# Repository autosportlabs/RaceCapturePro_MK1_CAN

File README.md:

CAN for RaceCapture/Pro MK1
====

CAN Bus interface module for RaceCapture/Pro MK1 only. This adds a single CAN bus interface channel that integrates with the SPI interface available on RJ45 port. 

See the LICENSE.txt for information on the technology license

Autosport Labs
http://www.autosportlabs.com

Building the CANx board
=======================

Parts are defined in the CANx.csv. 

* All resistors are 0603 5%
* All capacitors are 0603 X7R

Connecting CANx
===============

Connect a short (6" or shorter) RJ45 cable with pins wired straight through between RaceCapture/Pro MK1 and the X2 port of CANx. A simple ethernet 6" extension cable should work fine. 

The CAN bus connection is available on X1 and conforms to the same pinout as RaceCapture/Pro MK2. And, you can use the same CAN->OBDII cable used on the newer versions of RaceCapture/Pro.

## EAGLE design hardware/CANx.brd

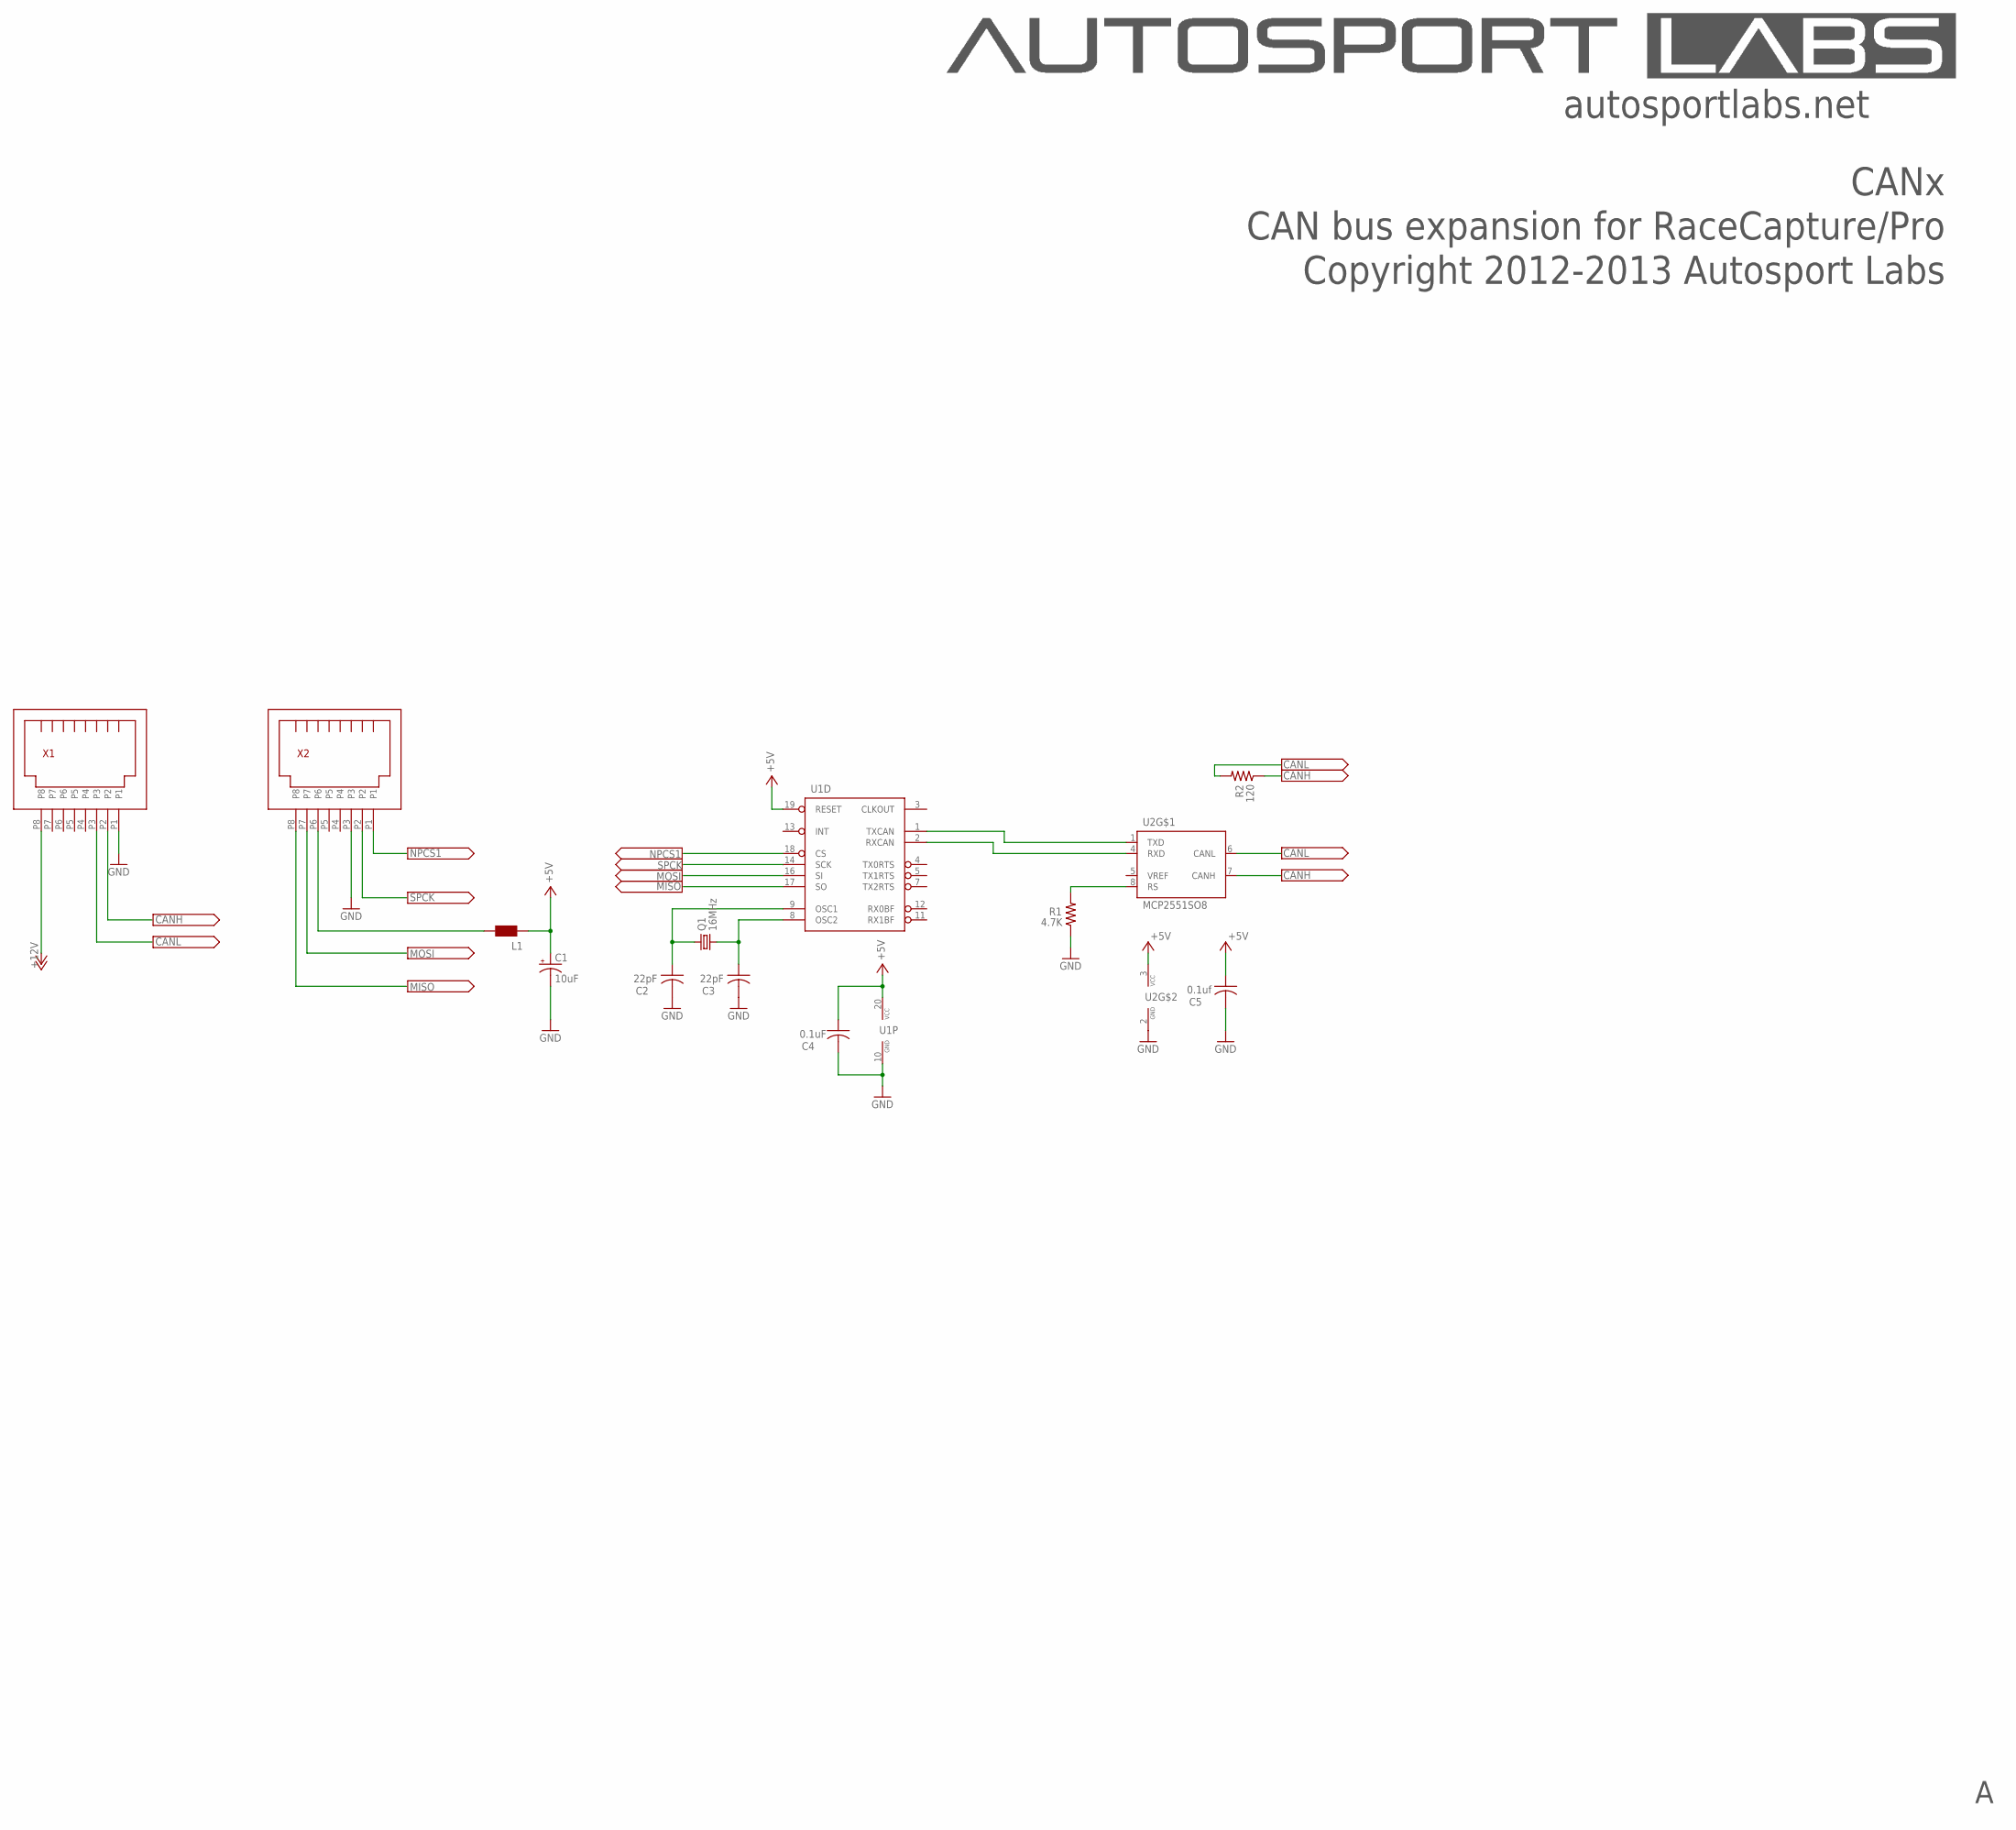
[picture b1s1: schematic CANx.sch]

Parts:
C1: 10uF; SMC_D
C2, C3: 22pF; C0603K
C4: 0.1uF; C0603K
C5: 0.1uf; C0603K
L1: WE-CBF_1812; 1812
Q1: 16MHz; CRYSTAL-SMD-5X3
R1: 4.7K; R0603
R2: 120; R0603
U1: MCP2515ST; TSSOP20
U2: MCP2551SO8; SO08
X1, X2: RJ45_RIGHT_ANGLEMOLEX_95001-2881; RJ45_RIGHT_ANGLE_MOLEX_95001-2881

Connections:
+5V: C1.+, C4.1, C5.1, L1.1, U1.19 (RESET), U1.20 (VCC), U2.3 (VCC)
+12V: X1.P8
CAN1_RX: U1.2 (RXCAN), U2.4 (RXD)
CAN1_TX: U1.1 (TXCAN), U2.1 (TXD)
CANH: R2.1, U2.7 (CANH), X1.P2
CANL: R2.2, U2.6 (CANL), X1.P3
GND: C1.-, C2.2, C3.2, C4.2, C5.2, R1.1, U1.10 (GND), U2.2 (GND), X1.P1, X2.P3
MISO: U1.17 (SO), X2.P8
MOSI: U1.16 (SI), X2.P7
unnamed: C2.1, Q1.3 (2), U1.9 (OSC1)
unnamed: C3.1, Q1.1, U1.8 (OSC2)
unnamed: L1.2, X2.P6
unnamed: R1.2, U2.8 (RS)
NPCS1: U1.18 (CS), X2.P1
SPCK: U1.14 (SCK), X2.P2

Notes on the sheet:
Copyright 2012-2013 Autosport Labs
CANx
autosportlabs.net
CAN bus expansion for RaceCapture/Pro

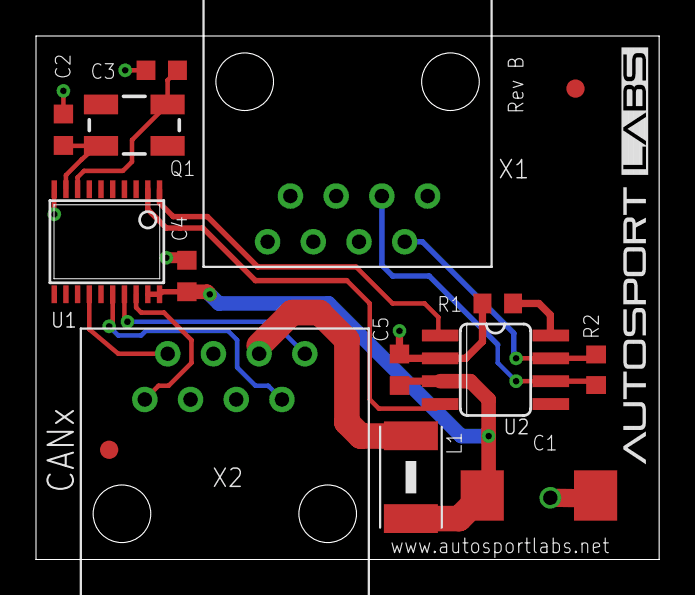
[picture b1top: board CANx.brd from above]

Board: 2 copper layers, 34.6 x 29.1 mm, 13 parts (0 on the bottom side), 14 nets.

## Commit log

2013-10-30 added initial files
2013-10-30 shrunk design of design to fit same enclosure as BT module
2013-10-30 fixed airwires
2013-10-30 added license; updated readme
2013-10-30 added board image
2014-03-05 updated CANx to use TSSOP-20 and center CAN connection plug to make it easier to identify orientation
2014-03-05 updated graphic
2017-01-19 Update README.md
    enhanced docs
2017-04-10 added BOM, updated readme
2017-04-10 added info on connecting
2017-04-16 add BOM
